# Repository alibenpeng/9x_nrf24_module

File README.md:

## JR/Graupner/FlySky/Turnigy compatible nRF24L01+ TX module

This module uses the very common and cheap nRF24L01+ modules available at various resellers as well as ebay.
It is very basic and does not include a bind button, so any binding has to be triggered by software.

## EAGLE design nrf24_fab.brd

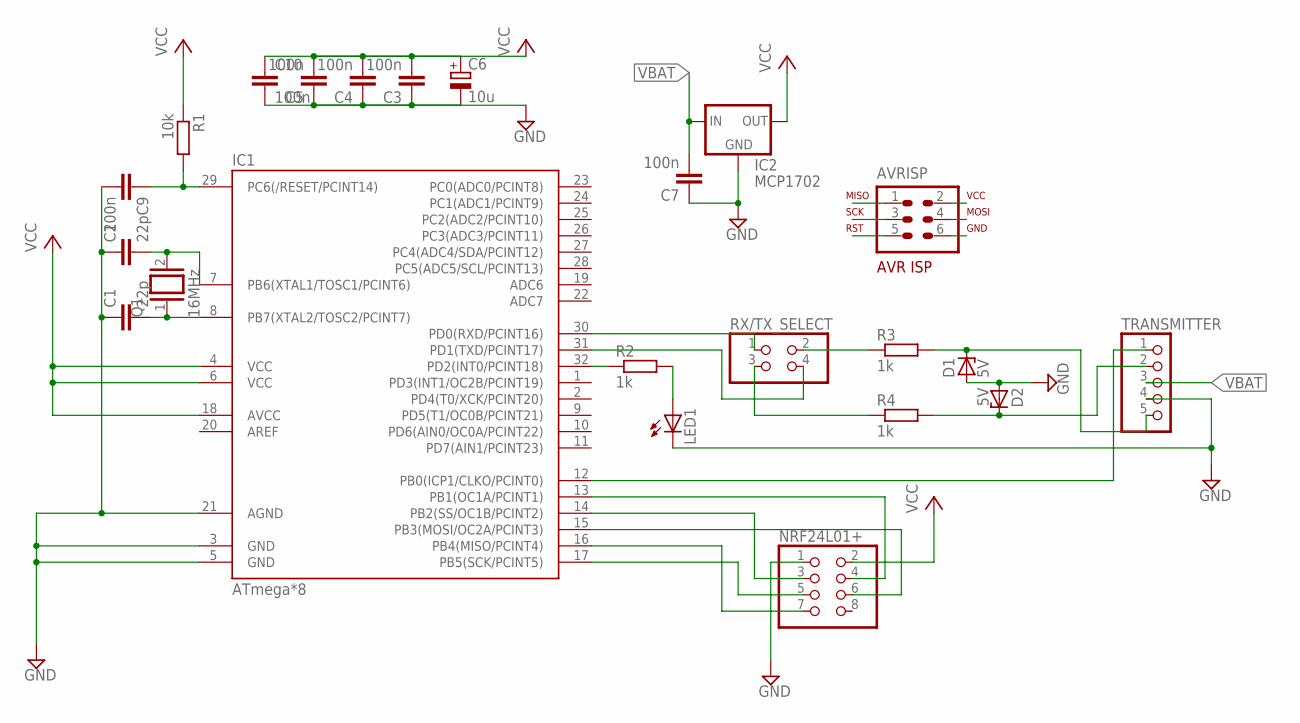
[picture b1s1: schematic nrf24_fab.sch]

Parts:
AVRISP: AVR-ISP-6VERT; AVR-ISP-6
C1, C2: 22p; C0805
C3, C4, C5, C7, C9, C10: 100n; C0805
C6: 10u; E2,5-6
D1, D2: 5V; SOD80C
IC1: ATmega*8; TQFP32-08
IC2: MCP1702; TO-92
LED1: LEDSMT1206; 1206
NRF24L01+: PINHD-2X4; 2X04
Q1: 16MHz; QS
R1: 10k; M0805
R2, R3, R4: 1k; M0805
RX/TX_SELECT: PINHD-2X2; 2X02
TRANSMITTER: PINHD-1X5; 1X05

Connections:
AVR_RXD: IC1.30 (PD0(RXD/PCINT16)), RX/TX_SELECT.1
AVR_TXD: IC1.31 (PD1(TXD/PCINT17)), RX/TX_SELECT.4
CE: IC1.14 (PB2(SS/OC1B/PCINT2)), NRF24L01+.3
CSN: IC1.13 (PB1(OC1A/PCINT1)), NRF24L01+.4
GND: AVRISP.6, C1.1, C2.1, C3.1, C4.1, C5.1, C6.-, C7.1, C9.2, C10.2, D1.A, D2.A, IC1.3 (GND), IC1.5 (GND), IC1.21 (AGND), IC2.1 (GND), LED1.C, NRF24L01+.1, TRANSMITTER.4
LED: LED1.A, R2.2
MISO: AVRISP.1, IC1.16 (PB4(MISO/PCINT4)), NRF24L01+.7
MOSI: AVRISP.4, IC1.15 (PB3(MOSI/OC2A/PCINT3)), NRF24L01+.6
unnamed: D2.C, R4.2, TRANSMITTER.2
unnamed: R4.1, RX/TX_SELECT.3
unnamed: R3.1, RX/TX_SELECT.2
unnamed: D1.C, R3.2, TRANSMITTER.5
unnamed: C1.2, IC1.8 (PB7(XTAL2/TOSC2/PCINT7)), Q1.1
unnamed: C2.2, IC1.7 (PB6(XTAL1/TOSC1/PCINT6)), Q1.2
PD2: IC1.32 (PD2(INT0/PCINT18)), R2.1
PPM: IC1.12 (PB0(ICP1/CLKO/PCINT0)), TRANSMITTER.1
RST: AVRISP.5, C9.1, IC1.29 (PC6(/RESET/PCINT14)), R1.2
SCK: AVRISP.3, IC1.17 (PB5(SCK/PCINT5)), NRF24L01+.5
VBAT: C7.2, IC2.2 (IN), TRANSMITTER.3
VCC: AVRISP.2, C3.2, C4.2, C5.2, C6.+, C10.1, IC1.4 (VCC), IC1.6 (VCC), IC1.18 (AVCC), IC2.3 (OUT), NRF24L01+.2, R1.1

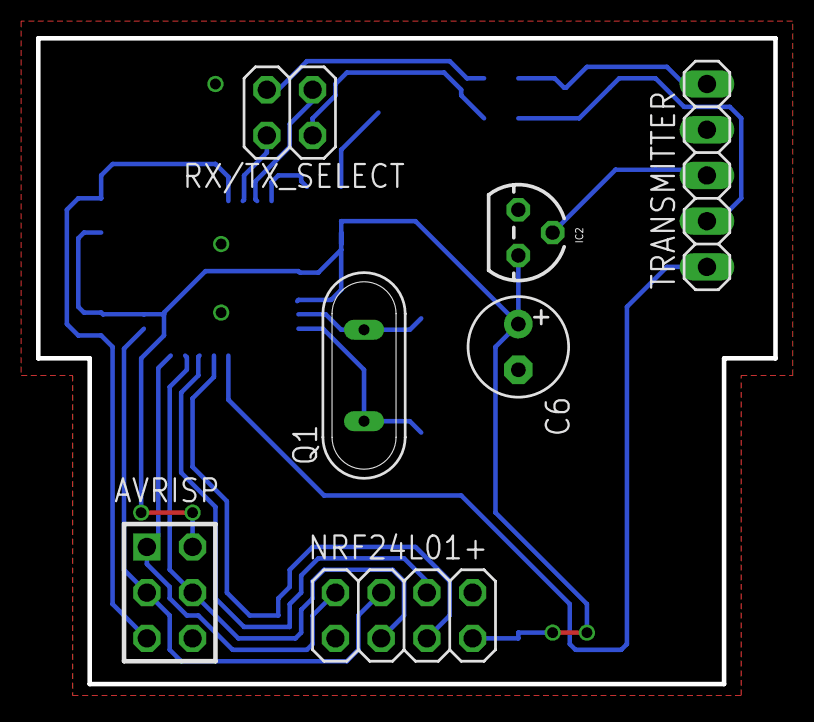
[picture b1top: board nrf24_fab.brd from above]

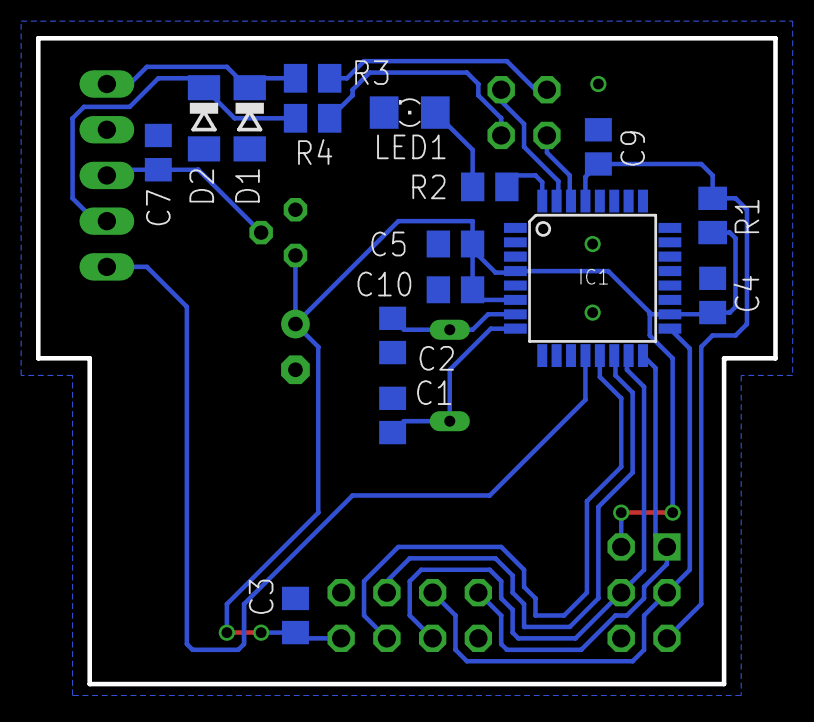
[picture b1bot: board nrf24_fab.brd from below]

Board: 2 copper layers, 41.0 x 35.9 mm, 23 parts (16 on the bottom side), 20 nets.

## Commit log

2014-06-30 renamed some files, split off a7105 board into separate repo.
2014-06-30 added parts values to schematic
2014-06-30 added readme
